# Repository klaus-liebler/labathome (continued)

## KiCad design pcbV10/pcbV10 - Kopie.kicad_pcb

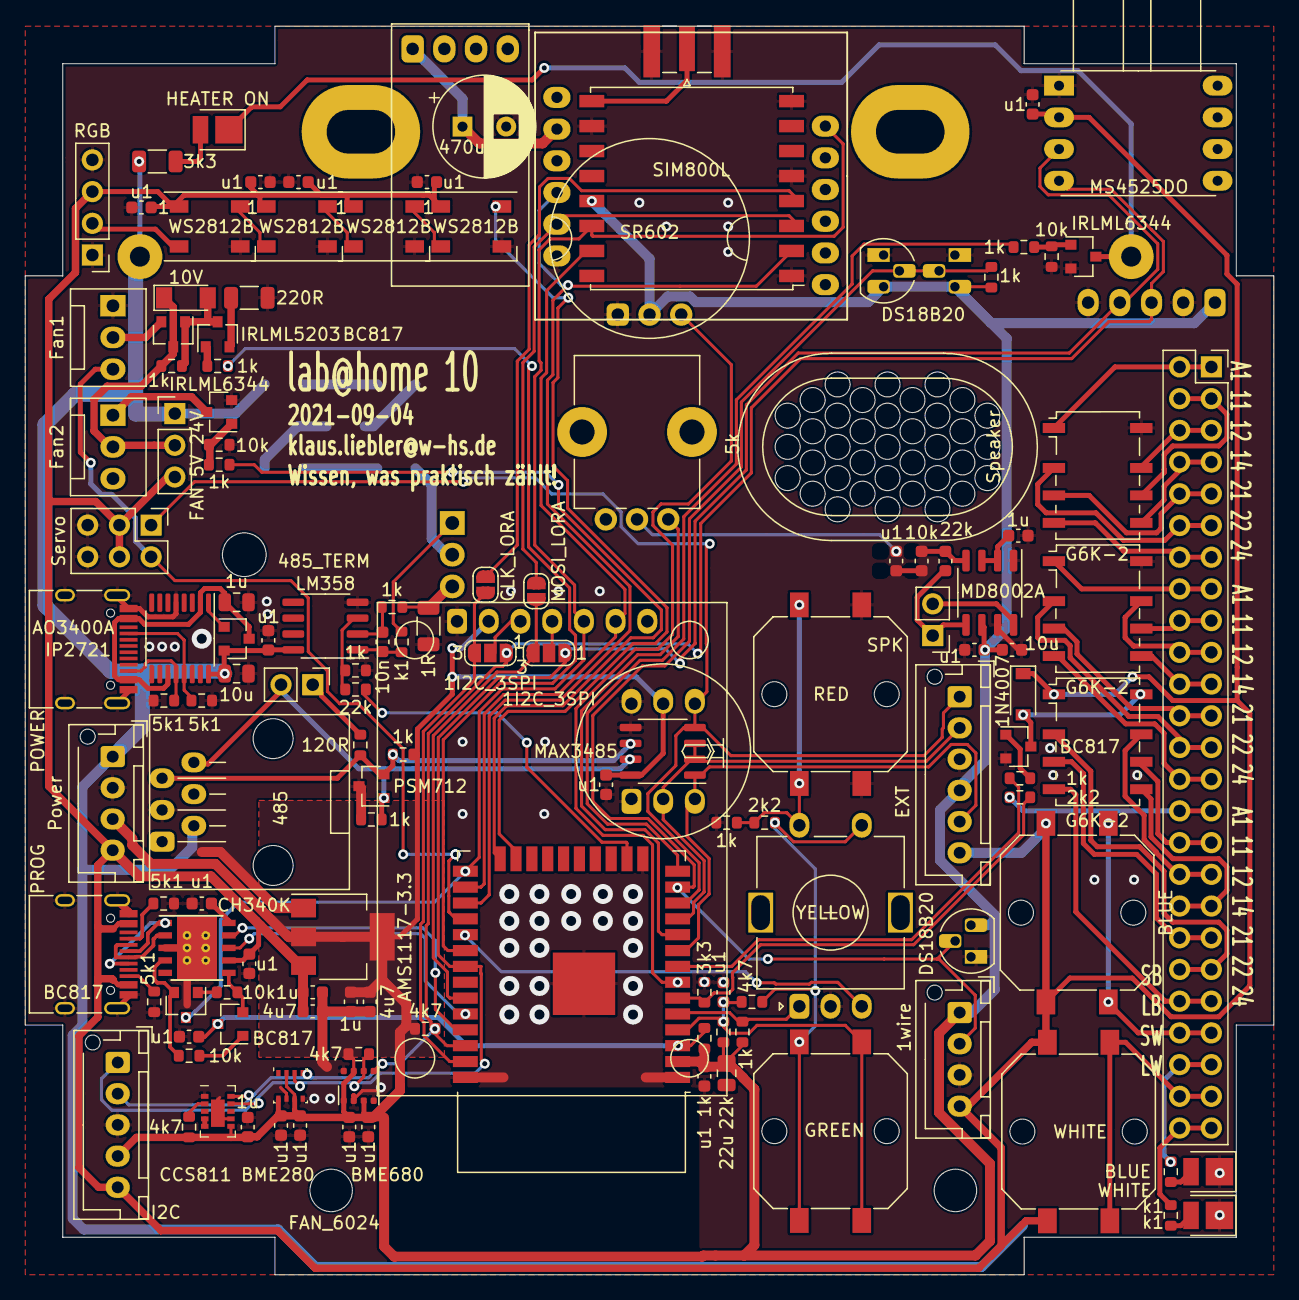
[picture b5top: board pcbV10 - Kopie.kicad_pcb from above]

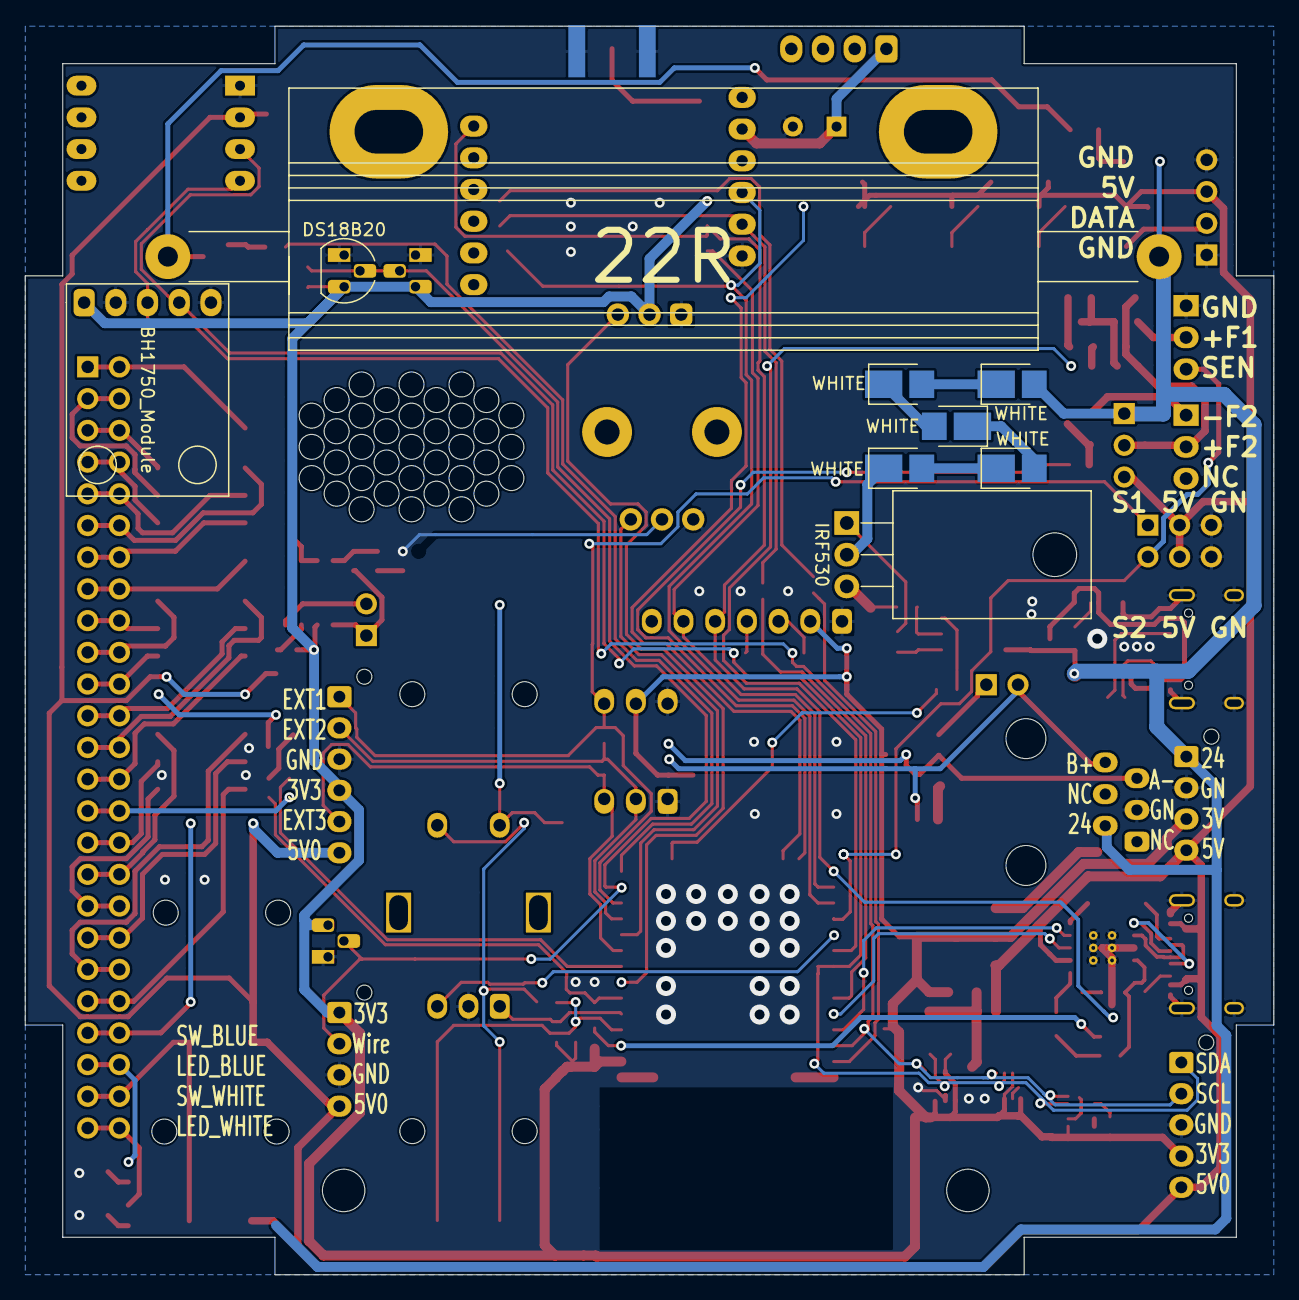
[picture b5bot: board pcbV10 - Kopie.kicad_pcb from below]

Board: 2 copper layers, 100.0 x 100.0 mm, 146 parts (9 on the bottom side), 116 nets.

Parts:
C1, C8: 4u7; C_0603_1608Metric
C2: 22u; C_0805_2012Metric
C3, C9, C23, C30: 1u; C_0603_1608Metric
C4, C5, C6, C7, C10, C11, C12, C13, C14, C15, C16, C18, C20, C21, C24, C25, C28, C29: u1; C_0603_1608Metric
C17: 1u; C_0805_2012Metric
C19: 10u; C_0805_2012Metric
C22: 10n; C_0603_1608Metric
C26: 10u; C_0603_1608Metric
C27: 470u; CP_Radial_D8.0mm_P3.50mm
D1, D2, D3, D15: WS2812B; LED_WS2812B_PLCC4_5.0x5.0mm_P3.2mm
D4: PSM712; SOT-23
D5: 1N4007; D_SOD-123
D6: HEATER ON; LED_PLCC_2835
D7: WHITE; LED_PLCC_2835
D8: BLUE; LED_PLCC_2835
D9: 10V; D_MiniMELF
D10, D11, D12, D13, D14: WHITE; LED_PLCC_2835_Handsoldering
GSM_Module1: SIM800L
J1: PROG; USB_C_Receptacle_HRO_TYPE-C-31-M-12
J2: Servo; PinHeader_2x03_P2.54mm_Vertical
J3: I2C; JST_XH_B5B-XH-AM_1x05_P2.50mm_Vertical
J4: 1wire; JST_XH_B4B-XH-AM_1x04_P2.50mm_Vertical
J5: EXT; JST_XH_B6B-XH-AM_1x06_P2.50mm_Vertical
J6: Power; JST_XH_B4B-XH-AM_1x04_P2.50mm_Vertical
J7: 485; WR_MJ_Modular_Jack_Vertical_Plastic_6P6C
J8: POWER; USB_C_Receptacle_HRO_TYPE-C-31-M-12
J9: RGB; PinHeader_1x04_P2.54mm_Vertical
J10: Fan1; FanPinHeader_1x03_P2.54mm_Vertical
J11: Fan2; FanPinHeader_1x03_P2.54mm_Vertical
J12: VPS; PinSocket_2x25_P2.54mm_Vertical
J13: SPK; PinHeader_1x02_P2.54mm_Vertical
J14: LoRa; SMA_Samtec_SMA-J-P-X-ST-EM1_EdgeMount
JP1: 485_TERM; PinHeader_1x02_P2.54mm_Vertical
JP2: FAN 5V 24V; PinHeader_1x03_P2.54mm_Vertical
JP3, JP4: 1I2C_3SPI; SolderJumper-3_P1.3mm_Open_RoundedPad1.0x1.5mm_NumberLabels
JP6: MOSI_LORA; SolderJumper-2_P1.3mm_Open_RoundedPad1.0x1.5mm
JP7: CLK_LORA; SolderJumper-2_P1.3mm_Open_RoundedPad1.0x1.5mm
K1, K2, K3: G6K-2; Relay_DPDT_Omron_G6K-2F-Y
Q1, Q2, Q4, Q6: BC817; SOT-23
Q3: AO3400A; SOT-23
Q5, Q9: IRLML6344; SOT-23
Q7: IRLML5203; SOT-23
Q8: IRF530; TO-220-3_Horizontal_TabDown
R1, R4, R11, R12, R14, R15, R17, R23, R27, R28, R29, R32, R34: 1k; R_0603_1608Metric
R2, R3, R9, R10: 5k1; R_0603_1608Metric
R5, R8, R21, R40: 4k7; R_0603_1608Metric
R6, R7, R16, R35: 10k; R_0603_1608Metric
R13: 120R; R_0603_1608Metric
R18: 22R; Resistor_100W
R19: 3k3; R_1206_3216Metric
R20, R26: 22k; R_0603_1608Metric
R22, R37: 2k2; R_0603_1608Metric
R24, R25, R31: k1; R_0603_1608Metric
R30: 220R; R_1206_3216Metric
R33: 1R; R_1206_3216Metric
R36: 3k3; R_0603_1608Metric
R38: 10k; C_0603_1608Metric
R39: 22k; C_0603_1608Metric
RV1: 5k; Potentiometer_Alps_RK09K_Single_Vertical
SP1: Speaker; SPEAKER_2415
SW1: BLUE; SW_Push_1P1T_NO_CK_PTS125Sx43PSMTR
SW2: YELLOW; RotaryEncoder_Alps_EC11E-Switch_Vertical_H20mm
SW3: GREEN; SW_Push_1P1T_NO_CK_PTS125Sx43PSMTR
SW4: RED; SW_Push_1P1T_NO_CK_PTS125Sx43PSMTR
SW5: WHITE; SW_Push_1P1T_NO_CK_PTS125Sx43PSMTR
U1: AMS1117-3.3; SOT-223-3_TabPin2
U2: ESP32-WROOM-32
U3: CH340K; SSOP-10_3.9x4.9mm_P1.00mm_EP
U4: MS4525DO
U5: INMP441_Module
U6: MAX3485; SO-8_3.9x4.9mm_P1.27mm
U7: BME680; Bosch_LGA-8_3x3mm_P0.8mm_ClockwisePinNumbering
U8: IP2721; TSSOP-16_4.4x5mm_P0.65mm
U9: BH1750_Module; GY-302
U10: SR602; PIR_Sensor_SR602
U11: LM358; SO-8_3.9x4.9mm_P1.27mm
U12, U13, U15: DS18B20; TO-92_HandSolder
U14: IPS_240_240; IPS_240_240_1.3
U16: MODULE_STEPDOWN
U17: RFM95W-868S2; HOPERF_RFM9XW_SMD
U18: MD8002A; SO-8_3.9x4.9mm_P1.27mm
U19: BME280; Bosch_LGA-8_2.5x2.5mm_P0.65mm_ClockwisePinNumbering
U20: CCS811; AMS_LGA-10-1EP_2.7x4mm_P0.6mm
X1: FAN_6024

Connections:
1wire: J4.2, R4.1, U2.13, U12.2, U13.2, U15.2
485_DE: J5.2, U2.11, U5.2, U6.2, U6.3
485_DI: J2.1, J5.1, U2.12, U5.4, U6.4
485_RO: J5.5, U2.9, U5.3, U6.1
+3V3: C2.1, C4.2, C8.2, C9.1, C11.2, C12.2, C13.2, C25.1, C26.1, C28.2, C29.2, C30.1, J3.4, J4.1, J5.4, J6.3, R1.2, R4.2, R5.2, R8.2, R12.1, R17.2, R20.1, R40.2, U1.2, U2.2, U5.5, U6.8, U7.2, U7.6, U7.8, U9.1, U10.2, U12.3, U13.3, U14.2, U15.3, U17.13, U18.6, U19.2, U19.6, U19.8, U20.6
+4V: C27.1, GSM_Module1.2, U16.1
+5V: C1.2, C3.1, C6.2, C7.2, C14.2, C15.2, C16.2, C18.2, D1.1, D2.1, D3.1, D5.1, D15.1, J1.A4, J1.A9, J1.B4, J1.B9, J2.3, J2.4, J3.5, J4.4, J5.6, J6.4, J9.3, JP2.3, K3.1, SW1.1, SW5.1, U1.3, U3.7, U4.2
+24V: C19.1, C21.1, D14.2, J6.1, J7.2, JP2.1, Q3.2, R18.1, R19.1, U8.16, U11.8
/C: JP3.2, U14.3
/D: JP4.2, U14.4
/DTR: Q2.2, R6.2, U3.4
/RTS: Q1.2, R7.2, U3.6
/VBUS: C17.2, J8.A4, J8.A9, J8.B4, J8.B9, Q3.3, U8.2, U8.11
/wireless/SPI_CLKx: JP7.2, U17.4
AUDIO: RV1.1, U2.10
FAN1_DRIVE: R28.2, U2.30
FAN1_SENSE: J2.2, J10.3, U2.28
FAN2_DRIVE: R34.2, U2.24
GND: C1.1, C2.2, C3.2, C4.1, C5.1, C6.1, C7.1, C8.1, C9.2, C10.2, C11.1, C12.1, C13.1, C14.1, C15.1, C16.1, C17.1, C18.1, C19.2, C20.1, C21.2, C23.2, C25.2, C26.2, C27.2, C28.1, C29.1, C30.2, D1.3, D2.3, D3.3, D4.3, D7.1, D8.1, D15.3, GSM_Module1.6, J1.A1, J1.A12, J1.B1, J1.B12, J1.S1, J2.5, J2.6, J3.3, J4.3, J5.3, J6.2, J7.3, J8.A1, J8.A12, J8.B1, J8.B12, J8.S1, J9.1, J9.4, J10.1, J14.2, K1.8, K2.8, Q4.2, Q5.2, Q9.2, R2.1, R3.1, R9.1, R10.1, R11.2, R16.1, R23.1, R27.1, R30.1, R33.2, R35.1, R36.1, RV1.3, SW2.C, SW4.1, U1.1, U2.1, U2.15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
HEATER: R15.2, U2.14
K1_11: J12.3, J12.4, K1.6
K1_12: J12.5, J12.6, K1.7
K1_14: J12.7, J12.8, K1.5
K1_21: J12.9, J12.10, K1.3
K1_22: J12.11, J12.12, K1.2
K1_24: J12.13, J12.14, K1.4
K1_A1: J12.1, J12.2, K1.1
K2_11: J12.17, J12.18, K2.6
K2_12: J12.19, J12.20, K2.7
K2_14: J12.21, J12.22, K2.5
K2_21: J12.23, J12.24, K2.3
K2_22: J12.25, J12.26, K2.2
K2_24: J12.27, J12.28, K2.4
K2_A1: J12.15, J12.16, K2.1
K3_11: J12.31, J12.32, K3.6
K3_12: J12.33, J12.34, K3.7
K3_14: J12.35, J12.36, K3.5
K3_21: J12.37, J12.38, K3.3
K3_22: J12.39, J12.40, K3.2
K3_24: J12.41, J12.42, K3.4
K3_A1: R36.2, R37.1, U2.6
K3_ON: R14.2, U2.8
LED_BLUE: J12.45, J12.46, R25.2
LED_RGB: D1.4, U2.23
LED_WHITE: J12.49, J12.50, R24.2
LED_WHITE_P: R26.2, U2.16
MOVE: U2.7, U10.3
unnamed: C10.1, U3.10
unnamed: C22.1, R32.1, U11.2
unnamed: C22.2, R31.1, U11.1
unnamed: C23.1, U18.2, U18.3
unnamed: C24.1, R38.2
unnamed: C24.2, RV1.2
unnamed: D1.2, D2.4
unnamed: D2.2, D3.4
unnamed: D5.2, K3.8, Q4.3
unnamed: D6.1, Q5.3, R18.2
unnamed: D6.2, R19.2
unnamed: D7.2, R24.1
unnamed: D8.2, R25.1
unnamed: D9.1, J11.2, JP2.2, Q7.3, R29.2
unnamed: D9.2, Q6.3, Q7.1, R29.1
unnamed: D10.1, D11.2
unnamed: D10.2, D12.1
unnamed: D11.1, D13.2
unnamed: D12.2, D14.1
unnamed: D13.1, Q8.2
unnamed: D15.2, J9.2
unnamed: D3.2, D15.4
unnamed: J1.A5, R2.2
unnamed: J1.A6, J1.B6, U3.1
unnamed: J1.A7, J1.B7, U3.2
unnamed: J1.B5, R3.2
unnamed: J8.A5, R9.2, U8.13
unnamed: J8.B5, R10.2, U8.12
unnamed: J10.2, Q7.2
unnamed: J11.1, Q9.3
unnamed: J12.29, J12.30, R37.2
unnamed: J13.1, R39.1, U18.5
unnamed: J13.2, U18.8
unnamed: J14.1, U17.9
unnamed: JP1.1, R13.2
unnamed: Q1.1, R6.1
unnamed: Q2.1, R7.1
unnamed: Q3.1, U8.1
unnamed: Q4.1, R14.1
unnamed: Q5.1, R15.1, R16.2
unnamed: Q6.1, R28.1
unnamed: Q6.2, R30.2
unnamed: Q8.1, R31.2
unnamed: Q8.3, R32.2, R33.1
unnamed: Q9.1, R34.1, R35.2
unnamed: R21.1, R22.2, SW2.S1, SW3.1
unnamed: R22.1, R23.2, SW2.S2, SW4.2
unnamed: R26.1, R27.2, U11.3
unnamed: R38.1, R39.2, U18.4
unnamed: R40.1, U20.2
unnamed: U20.4, U20.5
PROG_EN: C5.2, Q1.3, R1.1, U2.3
PROG_IO0: GSM_Module1.7, Q2.3, U2.25, U14.5, U17.14
PROG_RX: U2.35, U3.9
PROG_TX: U2.34, U3.8
ROT_A: R17.1, SW2.A, U2.5
ROT_B: SW2.B, U2.29
RS485A: D4.2, J7.5, R12.2, R13.1, U6.6
RS485B: D4.1, J7.6, JP1.2, R11.1, U6.7
SCL: J3.2, JP3.1, R8.1, U2.36, U4.4, U7.4, U9.3, U19.4, U20.10
SDA: J3.1, JP4.1, R5.1, U2.31, U4.3, U7.3, U9.4, U19.3, U20.9
SPI_CLK: JP3.3, JP7.1, U2.37
SPI_IO1: U2.26, U14.6, U17.15
SPI_MISO: GSM_Module1.4, U2.27, U17.2
SPI_MOSI: JP4.3, JP6.1, U2.33
SPI_MOSIx: GSM_Module1.5, JP6.2, U17.3
SW: C20.2, R20.2, R21.2, SW3.2, U2.4
SW_BLUE: J12.43, J12.44, SW1.2
SW_WHITE: J12.47, J12.48, SW5.2

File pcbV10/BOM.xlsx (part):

Reference | Quantity | Value | Footprint | Datasheet | AVAILABILITY | DESCRIPTION | MF | MP | PACKAGE | PRICE | Option | Description.1 | Height | Manufacturer_Name | Manufacturer_Part_Number
C1 C8 | 2 | 4u7 | Capacitor_SMD:C_0603_1608Metric | ~
C4 C5 C6 C7 C10 C11 C12 C13 C14 C15 C16 C18 C20 C24 C25 C28 C29 C31 C34 C35 | 20 | u1 | Capacitor_SMD:C_0603_1608Metric | ~
C17 C21 | 2 | 1u | Capacitor_SMD:C_1206_3216Metric | ~
C19 C22 C32 | 3 | 10u | Capacitor_SMD:C_1206_3216Metric | ~
C2 | 1 | 22u | Capacitor_SMD:C_0603_1608Metric | ~
C26 | 1 | 10u | Capacitor_SMD:C_0603_1608Metric | ~ |  |  |  |  |  |  | Sound only
C27 | 1 | 470u | Capacitor_THT:CP_Radial_D8.0mm_P3.50mm | ~
C3 C9 C23 C30 | 4 | 1u | Capacitor_SMD:C_0603_1608Metric | ~
C33 | 1 | u1 | Capacitor_SMD:C_0805_2012Metric | ~
C36 C37 | 2 | 22u | Capacitor_SMD:C_0805_2012Metric | ~
D1 D2 D3 D15 | 4 | WS2812B | LED_SMD:LED_WS2812B_PLCC4_5.0x5.0mm_P3.2mm | https://cdn-shop.adafruit.com/datasheets/WS2812B.pdf
D16 | 1 | Schttky | Diode_SMD:D_SOD-123 | ~
D4 | 1 | PSM712 | Package_TO_SOT_SMD:SOT-23 | http://www.onsemi.com/pub_link/Collateral/NUP2105L-D.PDF
D5 | 1 | 1N4007 | Diode_SMD:D_SOD-123 | ~
D6 | 1 | HEATER ON | liebler_OPTO:LED_PLCC_2835 | ~
D7 D10 D11 D12 D13 D14 | 6 | WHITE | liebler_OPTO:LED_PLCC_2835 | ~
D8 | 1 | BLUE | liebler_OPTO:LED_PLCC_2835 | ~
D9 | 1 | 10V | Diode_SMD:D_MiniMELF | ~
FID1 FID2 | 2 | Fiducial | Fiducial:Fiducial_1mm_Mask2mm | ~
GSM_Module1 | 1 | SIM800L | liebler_MODULES:SIM800L
IMG1 | 1 | Speaker | liebler_DRAWINGS:speaker | ~
IMG2 | 1 | Augenschutz | liebler_DRAWINGS:augenschutz | ~
IMG3 | 1 | HOT | liebler_DRAWINGS:hot | ~
IMG4 | 1 | WHS | liebler_DRAWINGS:LOGO_WHS | ~
J1 | 1 | PROG | liebler_CONN:USB_C_Receptacle_HRO_TYPE-C-31-M-12_IMPROVED | https://www.usb.org/sites/default/files/documents/usb_type-c.zip
J10 | 1 | Fan1 | Connector:FanPinHeader_1x03_P2.54mm_Vertical | ~
J11 | 1 | Fan2 | Connector:FanPinHeader_1x03_P2.54mm_Vertical | ~
J12 | 1 | VPS | Connector_PinSocket_2.54mm:PinSocket_2x25_P2.54mm_Vertical | ~
J13 | 1 | SPK | Connector_PinHeader_2.54mm:PinHeader_1x02_P2.54mm_Vertical | ~
J14 | 1 | LoRa | Connector_Coaxial:SMA_Samtec_SMA-J-P-X-ST-EM1_EdgeMount | ~
J15 | 1 | 1B 2A | Connector_Phoenix_MC:PhoenixContact_MCV_1,5_2-G-3.81_1x02_P3.81mm_Vertical | ~
J16 | 1 | BME280 | Connector_PinSocket_2.54mm:PinSocket_1x06_P2.54mm_Vertical | ~
J17 | 1 | CCS811 | Connector_PinSocket_2.54mm:PinSocket_1x08_P2.54mm_Vertical | ~
J2 | 1 | Servo | Connector_PinHeader_2.54mm:PinHeader_2x03_P2.54mm_Vertical | ~
J3 | 1 | I2C | Connector_JST:JST_XH_B5B-XH-AM_1x05_P2.50mm_Vertical | ~
J4 | 1 | 1wire | Connector_JST:JST_XH_B4B-XH-AM_1x04_P2.50mm_Vertical | ~
J5 | 1 | EXT | Connector_JST:JST_XH_B6B-XH-AM_1x06_P2.50mm_Vertical | ~
J6 | 1 | 5V 3V GN 24 | Connector_JST:JST_XH_B4B-XH-AM_1x04_P2.50mm_Vertical | ~
J7 | 1 | 485 | liebler_CONN:WR_MJ_Modular_Jack_Vertical_Plastic_6P6C | ~
J8 | 1 | POWER | liebler_CONN:USB_C_Receptacle_HRO_TYPE-C-31-M-12_IMPROVED | https://www.usb.org/sites/default/files/documents/usb_type-c.zip
J9 | 1 | RGB | Connector_PinHeader_2.54mm:PinHeader_1x04_P2.54mm_Vertical | ~
JP3 JP4 | 2 | 1I2C_3SPI | Jumper:SolderJumper-3_P1.3mm_Open_RoundedPad1.0x1.5mm_NumberLabels | ~
JP6 | 1 | MOSI_LORA | Jumper:SolderJumper-2_P1.3mm_Open_RoundedPad1.0x1.5mm | ~
JP7 | 1 | CLK_LORA | Jumper:SolderJumper-2_P1.3mm_Open_RoundedPad1.0x1.5mm | ~
K1 K2 K3 | 3 | G6K-2 | Relay_SMD:Relay_DPDT_Omron_G6K-2F-Y | http://omronfs.omron.com/en_US/ecb/products/pdf/en-g6k.pdf
L1 | 1 | 47u | Inductor_SMD:L_Wuerth_HCI-7030 | ~
L2 | 1 | 10uH | liebler_PASSIVES:ASPIAIG-Q8080 | ~
MK1 | 1 | ICS-43434 | liebler_SEMICONDUCTORS:MIC_ICS-43434 |  | Bad | Multi-Mode Microphone with I2S Digital Output | TDK-InvenSense | ICS-43434 | LGA-6 TDK-InvenSense | 2.43 USD
Q1 Q2 Q4 Q6 | 4 | BC817 | Package_TO_SOT_SMD:SOT-23 | https://www.onsemi.com/pub/Collateral/BC818-D.pdf
Q3 | 1 | AO3400A | Package_TO_SOT_SMD:SOT-23 | http://www.aosmd.com/pdfs/datasheet/AO3400A.pdf
Q5 Q9 | 2 | IRLML6344 | Package_TO_SOT_SMD:SOT-23 | https://www.infineon.com/dgdl/irlml0030pbf.pdf?fileId=5546d4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
Q7 | 1 | IRLML5203 | Package_TO_SOT_SMD:SOT-23 | https://www.infineon.com/dgdl/irlml5203pbf.pdf?fileId=5546d4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
R13 | 1 | 120R | Resistor_SMD:R_0603_1608Metric | ~
R1 R4 R11 R12 R14 R15 R17 R23 R28 R29 R34 R44 | 12 | 1k | Resistor_SMD:R_0603_1608Metric | ~
R18 | 1 | 22R | liebler_PASSIVES:Resistor_100W | ~
R19 | 1 | 3k3 | Resistor_SMD:R_1206_3216Metric | ~
R20 | 1 | 22k | Resistor_SMD:R_0603_1608Metric | ~
R5 R8 R21 R40 | 4 | 4k7 | Resistor_SMD:R_0603_1608Metric | ~
R22 R37 | 2 | 2k2 | Resistor_SMD:R_0603_1608Metric | ~
R24 R25 | 2 | k1 | Resistor_SMD:R_0603_1608Metric | ~
R27 | 1 | 1M | Resistor_SMD:R_0603_1608Metric | ~
R30 | 1 | 220R | Resistor_SMD:R_1206_3216Metric | ~
R31 | 1 | 51k | Resistor_SMD:R_0603_1608Metric | ~
R32 | 1 | 22R | Resistor_SMD:R_0603_1608Metric | ~
R33 | 1 | R68 | Resistor_SMD:R_1206_3216Metric | ~
R36 | 1 | 3k3 | Resistor_SMD:R_0603_1608Metric | ~
R38 | 1 | 10k | Capacitor_SMD:C_0603_1608Metric | ~ |  |  |  |  |  |  | Sound only
R39 | 1 | 22k | Capacitor_SMD:C_0603_1608Metric | ~ |  |  |  |  |  |  | Sound only
R41 R43 | 2 | M1 | Resistor_SMD:R_0603_1608Metric | ~
R42 | 1 | 2k2 | Capacitor_SMD:C_0603_1608Metric | ~ |  |  |  |  |  |  | Sound only
R45 | 1 | 6k8 | Resistor_SMD:R_0603_1608Metric | ~
R46 | 1 | 39k | Resistor_SMD:R_0603_1608Metric | ~
R47 | 1 | k47 | Resistor_SMD:R_0603_1608Metric | ~
R6 R7 R16 R26 R35 | 5 | 10k | Resistor_SMD:R_0603_1608Metric | ~
R2 R3 R9 R10 | 4 | 5k1 | Resistor_SMD:R_0603_1608Metric | ~
RV1 | 1 | 1k | Potentiometer_THT:Potentiometer_Alps_RK09K_Single_Vertical | ~ |  |  |  |  |  |  | Sound only
SP1 | 1 | Speaker | liebler_MECH:SPEAKER_2415 | ~
SW1 | 1 | BTN BLUE | liebler_MECH:SW_Push_1P1T_NO_CK_PTS125Sx43PSMTR | ~
SW10 | 1 | 5V FAN 24V | liebler_MECH:Switch_SS12D00 | ~
SW11 | 1 | 24V->5V | liebler_MECH:Switch_SS12D00 | ~
SW2 | 1 | YELLOW | liebler_MECH:RotaryEncoder_Alps_EC11E-Switch_Vertical_H20mm | ~
SW3 | 1 | GREEN | liebler_MECH:SW_Push_1P1T_NO_CK_PTS125Sx43PSMTR | ~
SW4 | 1 | RED | liebler_MECH:SW_Push_1P1T_NO_CK_PTS125Sx43PSMTR | ~
SW5 | 1 | BTN WHITE | liebler_MECH:SW_Push_1P1T_NO_CK_PTS125Sx43PSMTR | ~
SW6 | 1 | TERM ON | liebler_MECH:Switch_SS12D00 | ~
SW7 | 1 | LED HEATER | liebler_MECH:Switch_SS12D00 | ~
SW8 | 1 | REL_ROT | liebler_MECH:Switch_SS12D00 | ~
SW9 | 1 | SNS MOV | liebler_MECH:Switch_SS12D00 | ~
U1 | 1 | AMS1117-3.3 | Package_TO_SOT_SMD:SOT-223-3_TabPin2 | http://www.advanced-monolithic.com/pdf/ds1117.pdf
U10 | 1 | SR602 | liebler_MODULES:PIR_Sensor_SR602
U11 | 1 | MP4420 | Package_TO_SOT_SMD:TSOT-23-8
U12 U13 U15 | 3 | DS18B20 | Package_TO_SOT_THT:TO-92_HandSolder | http://datasheets.maximintegrated.com/en/ds/DS18B20.pdf
U14 | 1 | IPS_240_240 | liebler_OPTO:IPS_240_240_1.3
U16 | 1 | MODULE_STEPDOWN | liebler_MODULES:MODULE_STEPDOWN
U17 | 1 | RFM95W-868S2 | RF_Module:HOPERF_RFM9XW_SMD | https://www.hoperf.com/data/upload/portal/20181127/5bfcbea20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
U18 | 1 | MD8002A | Package_SO:SOIC-8_3.9x4.9mm_P1.27mm | https://www.sunrom.com/get/408862 |  |  |  |  |  |  |  | Audio Amplifier, SOP8 | 175 | Sunrom | MD8002A
U19 | 1 | BME280 | Package_LGA:Bosch_LGA-8_2.5x2.5mm_P0.65mm_ClockwisePinNumbering | https://ae-bst.resource.bosch.com/media/_tech/media/datashee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
U2 | 1 | ESP32-WROOM-32 | RF_Module:ESP32-WROOM-32 | https://www.espressif.com/sites/default/files/documentation/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
U20 | 1 | CCS811 | liebler_SEMICONDUCTORS:AMS_LGA-10-1EP_2.7x4mm_P0.6mm | http://ams.com/eng/Products/Environmental-Sensors/Air-Qualit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
U3 | 1 | CH340K | liebler_SEMICONDUCTORS:SSOP-10_3.9x4.9mm_P1.00mm_EP
U4 | 1 | MS4525DO | liebler_MODULES:MS4525DO
U5 | 1 | ZXLD1350 | Package_TO_SOT_SMD:SOT-23-5
U6 | 1 | MAX3485 | Package_SO:SOIC-8_3.9x4.9mm_P1.27mm | https://datasheets.maximintegrated.com/en/ds/MAX3483-MAX3491.pdf
U7 | 1 | BME680 | Package_LGA:Bosch_LGA-8_3x3mm_P0.8mm_ClockwisePinNumbering | https://ae-bst.resource.bosch.com/media/_tech/media/datashee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

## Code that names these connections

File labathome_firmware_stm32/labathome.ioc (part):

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Mcu.Name=STM32G431C(6-8-B)Ux
Mcu.Package=UFQFPN48
Mcu.UserName=STM32G431CBUx
PA0.GPIOParameters=GPIO_Label
PA0.GPIO_Label=ENC_A
PA0.Signal=S_TIM2_CH1
PA1.GPIOParameters=GPIO_Label
PA1.GPIO_Label=ENC_B
PA1.Signal=S_TIM2_CH2
PA10.GPIOParameters=GPIO_Label
PA10.GPIO_Label=BL_DRV3
PA10.Signal=S_TIM1_CH3
PA11.Mode=Device
PA11.Signal=USB_DM
PA12.Mode=Device
PA12.Signal=USB_DP
PA13.Signal=SYS_JTMS-SWDIO
PA14.Signal=SYS_JTCK-SWCLK
PA15.Mode=I2C
PA15.Signal=I2C1_SCL
PA2.GPIOParameters=GPIO_Label
PA2.GPIO_Label=Servo1
PA2.Signal=S_TIM15_CH1
PA3.GPIOParameters=GPIO_Label
PA3.GPIO_Label=Servo2
PA3.Signal=S_TIM15_CH2
PA4.Signal=COMP_DAC11_group
PA5.Signal=COMP_DAC12_group
PA6.GPIOParameters=GPIO_Label
PA6.GPIO_Label=Servo3
PA6.Signal=S_TIM16_CH1
PA7.GPIOParameters=GPIO_Label
PA7.GPIO_Label=Fan
PA7.Signal=S_TIM17_CH1
PA8.GPIOParameters=GPIO_Label
PA8.GPIO_Label=BL_DRV1
PA8.Signal=S_TIM1_CH1
PA9.GPIOParameters=GPIO_Label
PA9.GPIO_Label=BL_DRV2
PA9.Signal=S_TIM1_CH2
PB0.GPIOParameters=GPIO_Label
PB0.GPIO_Label=Hall2
PB0.Signal=S_TIM3_CH3
PB1.GPIOParameters=GPIO_Label
PB1.GPIO_Label=Hall3
PB1.Signal=S_TIM3_CH4
PB11.GPIOParameters=GPIO_Label
PB11.GPIO_Label=RELAY
PB11.Signal=GPIO_Output
PB12.GPIOParameters=GPIO_Label
PB12.GPIO_Label=BL_RESET
PB12.Signal=GPIO_Input
PB13.GPIOParameters=GPIO_Label
PB13.GPIO_Label=BL_FAULT
PB13.Signal=GPIO_Input
PB14.GPIOParameters=GPIO_Label
PB14.GPIO_Label=ADC1
PB14.Mode=IN5-Single-Ended
PB14.Signal=ADC1_IN5
PB15.GPIOParameters=GPIO_Label
PB15.GPIO_Label=ADC2
PB15.Signal=SharedAnalog_PB15
PB2.GPIOParameters=GPIO_Label
PB2.GPIO_Label=BRIGHTNESS
PB2.Mode=IN12-Single-Ended
PB2.Signal=ADC2_IN12
PB3.GPIOParameters=GPIO_Label
PB3.GPIO_Label=LED_INFO
PB3.Signal=GPIO_Output
PB4.Mode=Sink_AllSignals
PB4.Signal=UCPD1_CC2
PB5.GPIOParameters=GPIO_Label
PB5.GPIO_Label=BL_HALL3
PB5.Signal=S_TIM3_CH2
PB6.Mode=Sink_AllSignals
PB6.Signal=UCPD1_CC1
PB7.Mode=I2C
PB7.Signal=I2C1_SDA
PB8-BOOT0.GPIOParameters=GPIO_Label
PB8-BOOT0.GPIO_Label=BTN_RED
PB8-BOOT0.Signal=GPIO_Input
PB9.GPIOParameters=GPIO_Label
PB9.GPIO_Label=LED_POWER
PB9.Signal=S_TIM4_CH4
PC10.Mode=Asynchronous
PC10.Signal=UART4_TX
PC11.Mode=Asynchronous
PC11.Signal=UART4_RX
PC13.GPIOParameters=GPIO_Label
PC13.GPIO_Label=BTN_YEL
PC13.Signal=GPIO_Input
PC14-OSC32_IN.GPIOParameters=GPIO_Label
PC14-OSC32_IN.GPIO_Label=MOVEMENT_SENSOR
PC14-OSC32_IN.Signal=GPIO_Input
PC4.GPIOParameters=GPIO_Label
PC4.GPIO_Label=Heater
PC4.Signal=GPIO_Output
PC6.GPIOParameters=GPIO_Label
PC6.GPIO_Label=BL_ENABLE_OR_LED
PC6.Signal=GPIO_Output
PF0-OSC_IN.Mode=HSE-External-Oscillator
PF0-OSC_IN.Signal=RCC_OSC_IN
PF1-OSC_OUT.Mode=HSE-External-Oscillator
PF1-OSC_OUT.Signal=RCC_OSC_OUT
RCC.HSE_VALUE=8000000
RCC.SYSCLKFreq_VALUE=170000000
RCC.SYSCLKSource=RCC_SYSCLKSOURCE_PLLCLK
board=custom

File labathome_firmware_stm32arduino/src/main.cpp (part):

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float brushless_motor_velocity{0.0};
constexpr int POLE_PAIRS{7};
BLDCMotor bldcmotor = BLDCMotor(POLE_PAIRS);
BLDCDriver3PWM bldcdriver = BLDCDriver3PWM(PIN::BL_DRV1, PIN::BL_DRV2, PIN::BL_DRV3, PIN::BL_ENABLE);

constexpr time_t TIMEOUT_FOR_FAILSAFE{3000};
bool alreadySetToFailsafe{false};
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OPAMP_HandleTypeDef hopamp3;
HardwareSerial StepperSerial(PIN::UART3_RX, PIN::UART3_TX);
//Important: Define TX-Pin in the "const PinMap PinMap_UART_TX[]"-structure as OpenDrain
HardwareSerial ServoBusSerial(PIN::ADC1_U1R, PIN::ADC0_U1T);
// TMC2209Stepper stepperdriver(PIN::UART3_RX, PIN::UART3_TX, R_SENSE, DRIVER_ADDRESS);
HardwareSerial & stepper_serial_stream = StepperSerial;
TMC2209 stepperdriver;
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#if defined(ARDUINO_LABATHOME_15_0) || defined(ARDUINO_LABATHOME_15_1) || defined(ARDUINO_LABATHOME_15_2)
  digitalWrite(PIN::RELAY, e2s_buffer.Relay);
#endif
  digitalWrite(PIN::BL_RESET, e2s_buffer.Blreset);
#if defined(ARDUINO_LABATHOME_15_1) || defined(ARDUINO_LABATHOME_15_2) || defined(ARDUINO_LABATHOME_15_3)
  digitalWrite(PIN::BL_SLEEP, e2s_buffer.Blsleep);
  // digitalWrite(PIN::LCD_RESET, e2s_buffer.LcdReset);
#endif
  // TODO USBC
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  led->Loop(now);

  // I2C_SLAVE::e2s_buffer[E2S::HEATER_POS] = encoder.GetTicks(); // COMMENT OUT FOR TESTING ONLY
  s2e_buffer.ButtonRed = digitalRead(PIN::BTN_RED);
  s2e_buffer.ButtonYellow = (!digitalRead(PIN::BTN_YELLOW));
  s2e_buffer.Movement = digitalRead(PIN::MOVEMENT);
  s2e_buffer.Blfault = (!digitalRead(PIN::BL_FAULT));
  s2e_buffer.Rotenc = encoder.GetTicks();
  s2e_buffer.Brightness = analogRead(PIN::BRIGHTNESS);
  s2e_buffer.UsbpdVoltage_mv = PowerSink.activeVoltage;
  //s2e_buffer.Adc0 = analogRead(PIN::ADC_0_U1T);
  //s2e_buffer.Adc1 = analogRead(PIN::ADC_1_U1R);
#if defined(ARDUINO_LABATHOME_15_2) || defined(ARDUINO_LABATHOME_15_3)
  s2e_buffer.PIN_PB12 = digitalRead(PIN::PIN_PB12);
  s2e_buffer.Adc2_24V = analogRead(PIN::ADC_2_24V);
// s2e_buffer.Adc3_Bl_i_sense=analogRead(PIN::BL_ISENSE); wrong, we do not read the input directly, but the OPAMPs output
#endif

  if (now >= timeToPutActorsInFailsafe)
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    if (e2s_buffer.Heater > 0)
    {
      if(!heaterBefore){
        digitalWrite(PIN::HEATER, HIGH);
        log_info("Heater ON");
      }
      heaterBefore=true;
    }
    else
    {
      digitalWrite(PIN::HEATER, LOW);
      heaterBefore=false;
    }
  }
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    if(heaterBefore){
      log_info("Heater OFF");
    }
    digitalWrite(PIN::HEATER, LOW);
    heaterBefore=false;
  }
}
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void setup()
{

  led = new SINGLE_LED::M(PIN::LED_INFO, true, &WAITING_FOR_CONNECTION);
  led->Begin(millis(), &WAITING_FOR_CONNECTION, 10000);  
  Serial.begin(115200);
  
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  Serial4.printf("Application started Serial4.printf\n");//works
  
  log_info("Init gpio");
  pinMode(PIN::BTN_RED, INPUT);
  pinMode(PIN::BTN_YELLOW, INPUT);
  pinMode(PIN::MOVEMENT, INPUT);
  pinMode(PIN::BL_FAULT, INPUT);
  pinMode(PIN::HEATER, OUTPUT);
  pinMode(PIN::BRIGHTNESS, INPUT_ANALOG);

#if (defined(ARDUINO_LABATHOME_15_1) || defined(ARDUINO_LABATHOME_15_2))
  pinMode(PIN::RELAY, OUTPUT);
  pinMode(PIN::BL_SLEEP, OUTPUT);
  pinMode(PIN::BL_ISENSE, INPUT_ANALOG); // OPAMP2+
  pinMode(PIN::OPAMP3_M, INPUT_ANALOG);  // OPAMP3-
  pinMode(PIN::OPAMP3_P, INPUT_ANALOG);  // OPAMP3+
  pinMode(PIN::OPAMP3_Q, INPUT_ANALOG);  // OPAMP3+
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#ifdef ARDUINO_LABATHOME_15_2
  pinMode(PIN::ADC_2_24V, INPUT_ANALOG);
  pinMode(PIN::LCD_RESET, INPUT);
  pinMode(PIN::BL_RESET, OUTPUT);
  pinMode(PIN::PIN_PB12, INPUT);
  //pinMode(PIN::ADC_0, INPUT_ANALOG);
  //pinMode(PIN::ADC_1, INPUT_ANALOG);
#endif

#ifdef ARDUINO_LABATHOME_15_3
  pinMode(PIN::BL_SLEEP, OUTPUT);
  pinMode(PIN::BL_ISENSE, INPUT_ANALOG); // OPAMP2+
  pinMode(PIN::OPAMP3_M, INPUT_ANALOG);  // OPAMP3-
  pinMode(PIN::OPAMP3_P, INPUT_ANALOG);  // OPAMP3+
  pinMode(PIN::OPAMP3_Q, INPUT_ANALOG);  // OPAMP3+
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  HAL_ERROR_CHECK(HAL_OPAMP_Start(&hopamp2));
  pinMode(PIN::ADC_2_24V, INPUT_ANALOG);
  pinMode(PIN::LCD_RESET, INPUT);//because it is normally driven by the ESP32
  pinMode(PIN::BL_RESET, OUTPUT);
  pinMode(PIN::PIN_PB12, INPUT);
#endif

  log_info("Init Rotary Encoder");
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  TIM_SERVO->setPWM(SERVO3_CH, PC_3, 50, 0);

  TIM_FAN_LED_WHITE = new HardwareTimer(TIM15);
  TIM_FAN_LED_WHITE->setPWM(FAN_CH, PA_3_ALT1, 50, 0); // PA2 and PA3 changed from LabAtHome15.1 to 15.2
  TIM_FAN_LED_WHITE->setPWM(LED_WHITE_CH, PA_2_ALT1, 50, 0);

#elif defined(ARDUINO_LABATHOME_15_3)
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  TIM_SERVO->setPWM(SERVO3_CH, PC_3, 50, 0);

  TIM_FAN_LED_WHITE = new HardwareTimer(TIM15);
  TIM_FAN_LED_WHITE->setPWM(FAN_CH, PA_3_ALT1, 50, 0); // PA2 and PA3 changed from LabAtHome15.1 to 15.2
  TIM_FAN_LED_WHITE->setPWM(LED_WHITE_CH, PA_2_ALT1, 50, 0);

  log_info("Init ServoBus");
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  }
  log_info("Init StepperSerial");
  StepperSerial.begin(115200);
  pinMode(PIN::STEPPER_EN, OUTPUT);
  pinMode(PIN::FAN_SERVO4_STEPPER3_DIR, OUTPUT);
  pinMode(PIN::LED_WHITE_P_SERVO5_STEPPER3_STEP, OUTPUT);
  digitalWrite(PIN::STEPPER_EN, LOW); // Enable driver in hardware
  /*
    stepperdriver.begin();
    stepperdriver.toff(5);                 // Enables driver in software
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
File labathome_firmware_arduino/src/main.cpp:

#include <Arduino.h>
#include <Wire.h>
// I2C Konfiguration
constexpr uint8_t STM32_I2C_ADDRESS = 0x7E;
constexpr int I2C_SDA_PIN = 5;
constexpr int I2C_SCL_PIN = 6;
constexpr uint32_t I2C_FREQUENCY = 100000; // 100 kHz

// Pin Definitionen
constexpr gpio_num_t PIN_BTN_GREEN = (gpio_num_t)0;

constexpr gpio_num_t PIN_CANRX = (gpio_num_t)1;
constexpr gpio_num_t PIN_CANTX = (gpio_num_t)2;
constexpr gpio_num_t PIN_EXT_CS = (gpio_num_t)3;
constexpr gpio_num_t PIN_I2C_IRQ = (gpio_num_t)4;
constexpr gpio_num_t PIN_I2C_SDA = (gpio_num_t)5;
constexpr gpio_num_t PIN_I2C_SCL = (gpio_num_t)6;

constexpr gpio_num_t PIN_uSD_CMD = (gpio_num_t)7;
constexpr gpio_num_t PIN_LCD_CLK = (gpio_num_t)8;

constexpr gpio_num_t PIN_EXT_MISO = (gpio_num_t)9;
constexpr gpio_num_t PIN_EXT_CLK = (gpio_num_t)10;
constexpr gpio_num_t PIN_EXT_IO1 = (gpio_num_t)11;
constexpr gpio_num_t PIN_EXT_IO2 = (gpio_num_t)12;

constexpr gpio_num_t PIN_LED_WS2812 = (gpio_num_t)13;

constexpr gpio_num_t PIN_I2S_MCLK = (gpio_num_t)14;

constexpr gpio_num_t PIN_uSD_CLK = (gpio_num_t)15;
constexpr gpio_num_t PIN_uSD_D0 = (gpio_num_t)16;

constexpr gpio_num_t PIN_LCD_BL = (gpio_num_t)17;
constexpr gpio_num_t PIN_LCD_DC = (gpio_num_t)18;

constexpr gpio_num_t PIN_TXD0 = (gpio_num_t)43;
constexpr gpio_num_t PIN_RXD0 = (gpio_num_t)44;

constexpr gpio_num_t PIN_RS485_DI = (gpio_num_t)40;
constexpr gpio_num_t PIN_RS485_DE = (gpio_num_t)41;
constexpr gpio_num_t PIN_RS485_RO = (gpio_num_t)42;


constexpr gpio_num_t PIN_I2S_FS = (gpio_num_t)21;
constexpr gpio_num_t PIN_I2S_DAC = (gpio_num_t)45;
constexpr gpio_num_t PIN_EXT_MOSI = (gpio_num_t)46;
constexpr gpio_num_t PIN_I2S_ADC = (gpio_num_t)47;
constexpr gpio_num_t PIN_I2S_BCLK = (gpio_num_t)48;

constexpr gpio_num_t PIN_LCD_DAT = (gpio_num_t)38;
constexpr gpio_num_t PIN_LCD_RESET = (gpio_num_t)35;


constexpr gpio_num_t PIN_ONEWIRE = (gpio_num_t)39;
#include "communication.h"




void setup() {
    Serial.begin(115200);
    delay(1000);
    
    Serial.println("ESP32-S3 I2C Master Initialisierung");
    
    // I2C initialisieren
    Wire.begin(I2C_SDA_PIN, I2C_SCL_PIN);
    Wire.setClock(I2C_FREQUENCY);
    
    // Initialwerte für Send-Daten setzen
    initializeSendData();
    
    Serial.println("I2C Master bereit");
    Serial.printf("S2E_t Größe: %d Bytes\n", S2E_s);
    Serial.printf("E2S_t Größe: %d Bytes\n", E2S_s);
}

uint32_t lastDebugTime = 0;
void loop() {
    // Hauptkommunikationszyklus
    if (communicateWithSTM32()) {
        // Erfolgreiche Kommunikation
        processReceivedData();
        updateSendData();
        
        // Optional: Debug-Ausgabe
        if (millis() - lastDebugTime > 2000) {
            printDebugInfo();
            lastDebugTime = millis();
        }
    } else {
        // Fehlerbehandlung
        handleCommunicationError();
    }
    
    delay(10); // Kurze Pause zwischen den Zyklen
}



void processReceivedData() {
    // Hier die empfangenen Daten verarbeiten
    // Beispiel: Buttons, ADC-Werte, etc.
    
    if (receivedData.ButtonRed) {
        // Rote Button wurde gedrückt
        // Reaktion implementieren
    }
    
    if (receivedData.ButtonYellow) {
        // Gelbe Button wurde gedrückt
        // Reaktion implementieren
    }
    
    // ADC-Werte können hier verarbeitet werden
    // receivedData.Adc0, receivedData.Adc1, etc.
}

void updateSendData() {
    // Hier die zu sendenden Daten basierend auf
    // Programm-Logik aktualisieren
    
    // Beispiel: Fan-Geschwindigkeit basierend auf Temperatur steuern
    // if (receivedData.Adc2_24V > 2000) {
    //     sendData.Fan = 255; // Maximalgeschwindigkeit
    // } else {
    //     sendData.Fan = 128; // Halbe Geschwindigkeit
    // }
    
    // Beispiel: LED-Helligkeit vom Rotary Encoder übernehmen
    //sendData.LedPower = receivedData.Rotenc >> 8; // MSB des Encoders
}

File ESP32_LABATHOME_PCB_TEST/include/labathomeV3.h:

#include <inttypes.h>
#include <FastLED.h>
#include <Wire.h>
#include <OneWire.h>
#include <DallasTemperature.h>
#include <SparkFunBME280.h>
#include <BH1750.h>
#include <driver/mcpwm.h>
#include <driver/ledc.h>
#include <esp32-hal-ledc.h>

typedef uint8_t Pintype;

const Pintype PIN_R3_1 = 36;
const Pintype PIN_MOVEMENT = 39;
const Pintype PIN_POTI_T = 34;
const Pintype PIN_POTI = 35;
const Pintype PIN_SW_RED = 32;
const Pintype PIN_FAN_SENSE = 33;
const Pintype PIN_SERVO1 = 25;
const Pintype PIN_LED_STRIP = 26;
const Pintype PIN_SERVO2 = 27;
const Pintype PIN_ONEWIRE = 27;
const Pintype PIN_I2S_SCK = 14;
const Pintype PIN_FAN_DRIVE = 12;
const Pintype PIN_LED_POWER_WHITE = 13;
const Pintype PIN_LCD_MOSI = 23;
const Pintype PIN_I2C_SCL = 22;
const Pintype PIN_I2C_SDA = 21;
const Pintype PIN_LCD_RES = 19;
const Pintype PIN_LCD_CLK = 18;
const Pintype PIN_LCD_DC = 5;
const Pintype PIN_BUZZER = 17;
const Pintype PIN_R3_ON = 17;
const Pintype PIN_I2S_SD = 16;
const Pintype PIN_I2S_WS = 4;
const Pintype PIN_SW_GREEN = 0;
const Pintype PIN_HEATER = 2;
const Pintype PIN_SW_YELLOW = 15;


#define SERVO_MIN_PULSEWIDTH 500 //Minimum pulse width in microsecond
#define SERVO_MAX_PULSEWIDTH 2400 //Maximum pulse width in microsecond
#define SERVO_MAX_DEGREE 180 //Maximum angle in degree upto which servo can rotate

enum IO17_MODE
{
    RELAY,
    BUZZER,
};

enum class LED:uint8_t{
    LED_RED,
    LED_YELLOW,
    LED_GREEN,
    LED_3,
    LED_4,
    LED_5,
    LED_6,
    LED_7,
    

};

enum class Switch:uint8_t{
    SW_RED=PIN_SW_RED,
    SW_YELLOW=PIN_SW_YELLOW,
    SW_GREEN=PIN_SW_GREEN,
};

enum class Servo:uint8_t
{
    Servo1=0,
    Servo2=1,
};

class BSP
{    
    private:
        IO17_MODE io17;
    public:
        BSP(IO17_MODE io17):io17(io17)
        {

        }


        #define NUM_LEDS 8

        #define LED_TYPE WS2812B
        #define COLOR_ORDER GRB
        const uint8_t BRIGHTNESS = 50;
        const uint8_t FRAMES_PER_SECOND = 60;
        CRGBArray<NUM_LEDS> leds;
        // Setup a oneWire instance to communicate with any OneWire devices (not just Maxim/Dallas temperature ICs)
        OneWire oneWire();

        // Pass our oneWire reference to Dallas Temperature. 
        //DallasTemperature sensors(&oneWire);

        BME280 bme280;
        BH1750 bh1750;
        void initBoard()
        {
            
            pinMode(PIN_MOVEMENT, INPUT);
            pinMode(PIN_R3_1, INPUT);
            pinMode(PIN_POTI_T, ANALOG);
            pinMode(PIN_POTI, ANALOG);
            pinMode(PIN_SW_RED, INPUT_PULLUP);
            pinMode(PIN_FAN_SENSE, INPUT_PULLUP);
            FastLED.addLeds<LED_TYPE,PIN_LED_STRIP,COLOR_ORDER>(leds, NUM_LEDS).setCorrection(TypicalLEDStrip);
            FastLED.setBrightness( BRIGHTNESS );
            //oneWire.begin(27);
            pinMode(PIN_FAN_DRIVE, OUTPUT);
            pinMode(PIN_LED_POWER_WHITE, OUTPUT);
            Wire.begin(PIN_I2C_SDA, PIN_I2C_SCL, 100000);
            bme280.setI2CAddress(0x76); 
            if(bme280.beginI2C()){
                Serial.println("BME280 successfully initialized");
            }
            else
            {
                Serial.println("BME280 initialization failed");
            }
            if(bh1750.begin()){
                Serial.println("BH1750 successfully initialized");
            }
            else
            {
                Serial.println("BH1750 initialization failed");
            }
            
            
            if(io17==IO17_MODE::RELAY)
            {
                pinMode(PIN_R3_ON, OUTPUT);
            }
            
            pinMode(PIN_SW_GREEN, INPUT_PULLUP);
            pinMode(PIN_HEATER, OUTPUT);
            pinMode(PIN_SW_YELLOW, INPUT_PULLUP);

            //Servos
            mcpwm_gpio_init(MCPWM_UNIT_0, MCPWM0A, PIN_SERVO1);
            mcpwm_gpio_init(MCPWM_UNIT_0, MCPWM0B, PIN_SERVO2);
            mcpwm_config_t pwm_config;
            pwm_config.frequency = 50;    //frequency = 50Hz, i.e. for every servo motor time period should be 20ms
            pwm_config.cmpr_a = 0;    //duty cycle of PWMxA = 0
            pwm_config.cmpr_b = 0;    //duty cycle of PWMxb = 0
            pwm_config.counter_mode = MCPWM_UP_COUNTER;
            pwm_config.duty_mode = MCPWM_DUTY_MODE_0;
            mcpwm_init(MCPWM_UNIT_0, MCPWM_TIMER_0, &pwm_config);    //Configure PWM0A & PWM0B with above settings   

            //LED
            ledc_timer_config_t power_ledc_timer;
            power_ledc_timer.duty_resolution = LEDC_TIMER_13_BIT; // resolution of PWM duty
            power_ledc_timer.freq_hz = 5000;                      // frequency of PWM signal
            power_ledc_timer.speed_mode = LEDC_HIGH_SPEED_MODE;           // timer mode
            power_ledc_timer.timer_num = LEDC_TIMER_0;            // timer index
            ledc_timer_config(&power_ledc_timer);

            ledc_channel_config_t ledc_channel;
            ledc_channel.channel    = LEDC_CHANNEL_0;
            ledc_channel.duty       = 0;
            ledc_channel.gpio_num   = PIN_LED_POWER_WHITE;
            ledc_channel.speed_mode = LEDC_HIGH_SPEED_MODE;
            ledc_channel.hpoint     = 0;
            ledc_channel.timer_sel  = LEDC_TIMER_0;

            ledc_channel_config(&ledc_channel);

            if(io17==IO17_MODE::BUZZER)
            {
                ledcSetup(2, 2000, 8);
                ledcAttachPin(PIN_BUZZER, 2);
            }
        
        }

        void startBuzzer(double freq)
        {
            if(io17!=IO17_MODE::BUZZER) return;
            ledcWriteTone(2, freq);
        }

        void endBuzzer()
        {
            ledcWrite(2, 0);
        }
        
        void setLEDState(LED led, CRGB state)
        {
            leds[(uint8_t)led]=state;
            FastLED.show();
        }

        void setRELAYState(bool state)
        {
            if(io17!=IO17_MODE::RELAY) return;
            digitalWrite(PIN_R3_ON, state);
        }

        void setLED_POWER_WHITE_DUTY(uint8_t percent)
        {
            if(percent>100) percent=100;
            uint32_t duty =((1<<13)*percent)/100;
            ledc_set_duty(LEDC_HIGH_SPEED_MODE, LEDC_CHANNEL_0, duty);
            ledc_update_duty(LEDC_HIGH_SPEED_MODE, LEDC_CHANNEL_0);
        }
        bool getButtonIsPressed(Switch theSwitch)
        {
            return !digitalRead((uint8_t)theSwitch);
        }

        bool isMovementDetected()
        {
            return digitalRead(PIN_MOVEMENT);
        }

        void setServo (Servo servo, uint32_t angle_0_to_180)
        {
            uint32_t cal_pulsewidth = (SERVO_MIN_PULSEWIDTH + (((SERVO_MAX_PULSEWIDTH - SERVO_MIN_PULSEWIDTH) * (angle_0_to_180)) / (SERVO_MAX_DEGREE)));
            switch(servo)
            {
                case Servo::Servo1:
                    mcpwm_set_duty_in_us(MCPWM_UNIT_0, MCPWM_TIMER_0, MCPWM_OPR_A, cal_pulsewidth);
                    break;
                case Servo::Servo2:
                    mcpwm_set_duty_in_us(MCPWM_UNIT_0, MCPWM_TIMER_0, MCPWM_OPR_B, cal_pulsewidth);
                    break;
                default:
                    break;
            }
        }
};

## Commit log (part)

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2020-04-18 Improved Layout
2020-05-07 PCB REV2
2020-05-07 testwebserver initial
2020-06-18 PCB V2 RC1
2020-06-18 First fuction block implementation
2020-06-18 VSCode Workspace
2020-06-19 Better 3D models
2020-06-22 PCB V2 as ordered
2020-06-28 Slight optimizations in PCB
2020-07-25 Case design
2020-07-25 Firmware Various Updates
2020-08-11 PCB V4 as ordered at JLCPCB
2020-08-11 Arduino based test software for produced boards
2020-08-25 PCB last version without SMD
2020-08-29 PCB labathomev5 as ordered at jlcpcb
2020-09-20 Various big changes (sorry for beeing rude here...)
2020-09-26 labathome - first break through - simple and/or/rs working :-)
2020-10-02 PID-Controller
2020-10-14 Overall unspecific update
2020-10-16 V0.1 ready for testing :-)
2020-11-02 Simulation Mode in WebUI
2020-11-14 heaterEmergencyShutdown fix
2020-12-13 Bump ini from 1.3.5 to 1.3.8 in /rtttl2binary
    Bumps [ini](https://github.com/isaacs/ini) from 1.3.5 to 1.3.8.
    - [Release notes](https://github.com/isaacs/ini/releases)
    - [Commits](https://github.com/isaacs/ini/compare/v1.3.5...v1.3.8)
2021-03-10 Bump elliptic from 6.5.3 to 6.5.4 in /webui
    Bumps [elliptic](https://github.com/indutny/elliptic) from 6.5.3 to 6.5.4.
    - [Release notes](https://github.com/indutny/elliptic/releases)
    - [Commits](https://github.com/indutny/elliptic/compare/v6.5.3...v6.5.4)
2021-03-31 Bump y18n from 3.2.1 to 3.2.2 in /rtttl2binary
    Bumps [y18n](https://github.com/yargs/y18n) from 3.2.1 to 3.2.2.
    - [Release notes](https://github.com/yargs/y18n/releases)
    - [Changelog](https://github.com/yargs/y18n/blob/master/CHANGELOG.md)
    - [Commits](https://github.com/yargs/y18n/commits)
2021-05-11 Bump hosted-git-info from 2.8.8 to 2.8.9 in /webui
    Bumps [hosted-git-info](https://github.com/npm/hosted-git-info) from 2.8.8 to 2.8.9.
    - [Release notes](https://github.com/npm/hosted-git-info/releases)
    - [Changelog](https://github.com/npm/hosted-git-info/blob/v2.8.9/CHANGELOG.md)
    - [Commits](https://github.com/npm/hosted-git-info/compare/v2.8.8...v2.8.9)
2021-05-11 Bump hosted-git-info from 2.8.8 to 2.8.9 in /rtttl2binary
    Bumps [hosted-git-info](https://github.com/npm/hosted-git-info) from 2.8.8 to 2.8.9.
    - [Release notes](https://github.com/npm/hosted-git-info/releases)
    - [Changelog](https://github.com/npm/hosted-git-info/blob/v2.8.9/CHANGELOG.md)
    - [Commits](https://github.com/npm/hosted-git-info/compare/v2.8.8...v2.8.9)
2021-06-01 lab@home5.3 as ordered at jlcpcb
2021-06-04 I2S-Amp --> Analog (damn cheap) Amp
2021-08-09 labathome V6 as ordered at JLCPCB
2021-08-12 Bump path-parse from 1.0.6 to 1.0.7 in /rtttl2binary
    Bumps [path-parse](https://github.com/jbgutierrez/path-parse) from 1.0.6 to 1.0.7.
    - [Release notes](https://github.com/jbgutierrez/path-parse/releases)
    - [Commits](https://github.com/jbgutierrez/path-parse/commits/v1.0.7)
    ---
    updated-dependencies:
    - dependency-name: path-parse
2021-09-14 Switched to CMAKE
2021-09-14 Added option description for PCB
2021-11-25 pcb V10 as ordered at JLCPCB
2022-01-01 labathome v11 as ordered @ JLCPCB
2022-01-07 Moved all components to esp-idf components repository
2022-02-11 Bump node-sass from 4.14.1 to 7.0.0 in /labathome_webui
    Bumps [node-sass](https://github.com/sass/node-sass) from 4.14.1 to 7.0.0.
    - [Release notes](https://github.com/sass/node-sass/releases)
    - [Changelog](https://github.com/sass/node-sass/blob/master/CHANGELOG.md)
    - [Commits](https://github.com/sass/node-sass/compare/v4.14.1...v7.0.0)
    ---
    updated-dependencies:
2022-03-02 All SMD components orderable @ JLCPCB
2022-03-27 Updated capacitor JLCPCB, Removed unnecessary Files
2022-03-30 Bump minimist from 1.2.5 to 1.2.6 in /labathome_webui
    Bumps [minimist](https://github.com/substack/minimist) from 1.2.5 to 1.2.6.
    - [Release notes](https://github.com/substack/minimist/releases)
    - [Commits](https://github.com/substack/minimist/compare/1.2.5...1.2.6)
    ---
    updated-dependencies:
    - dependency-name: minimist
2022-04-04 Migration to IDF5.0
2022-04-08 Sicherung
2022-05-06 Various
2022-05-12 Bump copy-props from 2.0.4 to 2.0.5 in /rtttl2binary
    Bumps [copy-props](https://github.com/gulpjs/copy-props) from 2.0.4 to 2.0.5.
    - [Release notes](https://github.com/gulpjs/copy-props/releases)
    - [Changelog](https://github.com/gulpjs/copy-props/blob/master/CHANGELOG.md)
    - [Commits](https://github.com/gulpjs/copy-props/compare/2.0.4...2.0.5)
    ---
    updated-dependencies:
2022-05-12 Bump copy-props from 2.0.4 to 2.0.5 in /labathome_webui
    Bumps [copy-props](https://github.com/gulpjs/copy-props) from 2.0.4 to 2.0.5.
    - [Release notes](https://github.com/gulpjs/copy-props/releases)
    - [Changelog](https://github.com/gulpjs/copy-props/blob/master/CHANGELOG.md)
    - [Commits](https://github.com/gulpjs/copy-props/compare/2.0.4...2.0.5)
    ---
    updated-dependencies:
2022-05-12 Bump lodash from 4.17.20 to 4.17.21 in /labathome_webui
    Bumps [lodash](https://github.com/lodash/lodash) from 4.17.20 to 4.17.21.
    - [Release notes](https://github.com/lodash/lodash/releases)
    - [Commits](https://github.com/lodash/lodash/compare/4.17.20...4.17.21)
    ---
    updated-dependencies:
    - dependency-name: lodash
2022-05-12 Refactoring; configmanager, otamanager
2022-05-12 Deleted old pcb version - never go back to these times ;-)
2022-05-23 Reorganisation
2022-06-09 component for AHT21 sensor
2022-06-22 Bugfix: digital amplifier not in standby
2022-07-01 Boris Integration; some code rework
2022-07-19 Getting ptnchen running; borisuserdlls
2022-07-20 Addes ptnchen pcb
2022-09-03 Minor fixes
2022-09-08 Updated PCB: nRF24l01, SIM7080, LoRa module
2022-11-10 Bump minimatch from 3.0.4 to 3.1.2 in /rtttl2binary
    Bumps [minimatch](https://github.com/isaacs/minimatch) from 3.0.4 to 3.1.2.
    - [Release notes](https://github.com/isaacs/minimatch/releases)
    - [Commits](https://github.com/isaacs/minimatch/compare/v3.0.4...v3.1.2)
    ---
    updated-dependencies:
    - dependency-name: minimatch
2022-12-07 Bump decode-uri-component from 0.2.0 to 0.2.2 in /rtttl2binary
    Bumps [decode-uri-component](https://github.com/SamVerschueren/decode-uri-component) from 0.2.0 to 0.2.2.
    - [Release notes](https://github.com/SamVerschueren/decode-uri-component/releases)
    - [Commits](https://github.com/SamVerschueren/decode-uri-component/compare/v0.2.0...v0.2.2)
    ---
    updated-dependencies:
    - dependency-name: decode-uri-component
2022-12-07 Bump qs and express in /testwebserver
    Bumps [qs](https://github.com/ljharb/qs) to 6.11.0 and updates ancestor dependency [express](https://github.com/expressjs/express). These dependencies need to be updated together.
    Updates `qs` from 6.7.0 to 6.11.0
    - [Release notes](https://github.com/ljharb/qs/releases)
    - [Changelog](https://github.com/ljharb/qs/blob/main/CHANGELOG.md)
    - [Commits](https://github.com/ljharb/qs/compare/v6.7.0...v6.11.0)
    Updates `express` from 4.17.1 to 4.18.2
2022-12-08 LTSpice Simulation & minor optical fixes
2023-01-24 Bump cookiejar from 2.1.3 to 2.1.4 in /labathome_webui
    Bumps [cookiejar](https://github.com/bmeck/node-cookiejar) from 2.1.3 to 2.1.4.
    - [Release notes](https://github.com/bmeck/node-cookiejar/releases)
    - [Commits](https://github.com/bmeck/node-cookiejar/commits)
    ---
    updated-dependencies:
    - dependency-name: cookiejar
2023-08-08 Modbus Firmware
2023-08-09 Switch UART
    Programming port (GPIO1 and 3) are the modbus port now. console output shoud be routed to GPIO 21 (menuconfig
2023-09-03 Udated flash website
2023-09-24 Reading DS18B20
2023-10-09 New sensor values
2023-10-20 Fix Movement Sensor
2024-06-27 PCB_v15 wip
2024-06-28 pcb15 WIP
2024-07-01 labathome15 v0.0.1
2024-07-05 initial version of labathome_firmware_stm32
2024-07-05 labathome_pcb15 ready for first review
2024-07-05 labathome_pcb15
2024-07-06 labathome_pcb5 ready for review, 2nd
2024-07-08 Various PCB and Code updates after review from Jana Marie Hemsing. Big Thankyou
2024-07-08 Ooops, did not test to build it...
2024-07-08 Final PCB as ordered @ JLCPCB
2024-07-16 Various updates
2024-08-16 Added stm32 arduino firmware
2024-08-20 Updates in PCB, arduino test firmware
2024-08-20 Cosmetics
2024-08-20 Re-enumerate Servos and Fans
2024-08-20 Update Modbus firmware (untested)
2024-08-22 Cosmetics (improved ground planes, more vias)
2024-08-22 Various bugfixes for the stm32 arduino firmware
2024-08-23 Various Bugfixes after testing modbus and open loop heater experiment
2024-08-29 Show state on display; minor cosmetics
2024-08-29 nau88c22 45deg
2024-09-01 Fix Easteregg
2024-09-01 OutputOneLineStatus -->DoMonitoring
2024-09-02 PCB update IP5306 I2C
2024-09-03 4 Layers
2024-09-04 labathome 15.1 as ordered @ JLCPCB
2024-09-05 Update LabathomeMapping.md
    Add general informations and functioncodes
2024-09-10 brushless motor firmware
2024-09-15 lsm6ds3 + kalman
2024-09-17 Labathome Heater control loop working point
2024-09-20 Bump vite from 5.3.3 to 5.4.6 in /espidf-component-labathome/web
    Bumps [vite](https://github.com/vitejs/vite/tree/HEAD/packages/vite) from 5.3.3 to 5.4.6.
    - [Release notes](https://github.com/vitejs/vite/releases)
    - [Changelog](https://github.com/vitejs/vite/blob/v5.4.6/packages/vite/CHANGELOG.md)
    - [Commits](https://github.com/vitejs/vite/commits/v5.4.6/packages/vite)
    ---
    updated-dependencies:
2024-09-24 Bump rollup from 4.18.1 to 4.22.4 in /espidf-component-labathome/web
    Bumps [rollup](https://github.com/rollup/rollup) from 4.18.1 to 4.22.4.
    - [Release notes](https://github.com/rollup/rollup/releases)
    - [Changelog](https://github.com/rollup/rollup/blob/master/CHANGELOG.md)
    - [Commits](https://github.com/rollup/rollup/compare/v4.18.1...v4.22.4)
    ---
    updated-dependencies:
2024-10-01 Code to test the accessability of a serial port
2024-10-03 ec11 smd, LCD Reset from ESP32 with jumper, six servos
2024-10-11 Updated PCB, sensprs as JSON
2024-10-13 IP5306
2024-10-14 Pushed microSD up
2024-10-17 TPS2116
2024-10-17 Labathome 15.2 as ordered at JLCPCB
2024-10-31 Database based build process
2024-11-04 PCB 15.2 as ordered @ JLCPCB; database backed build process
2024-11-05 New Function Block ConstantINTEGER
2024-11-06 Fixes for 15.2 and 15.ß
2024-11-11 Fixes / Refactoring
2024-11-15 Added Stepper Motors (initial)
2024-11-16 Fixes
2024-11-22 PCB update; DRC check passed; optimized routing
2024-11-22 Layout improvement; use common enable signal for steppers
2024-11-26 Optimized PCB
2024-11-26 Prepared new 15_3 board version with stepper motor drivers
2024-11-26 Added flatbuffers
2024-11-26 Added SVG collection from fontawesome
2024-11-26 Bump vite from 5.3.3 to 5.4.11 in /espidf-component-labathome/web
    Bumps [vite](https://github.com/vitejs/vite/tree/HEAD/packages/vite) from 5.3.3 to 5.4.11.
    - [Release notes](https://github.com/vitejs/vite/releases)
    - [Changelog](https://github.com/vitejs/vite/blob/main/packages/vite/CHANGELOG.md)
    - [Commits](https://github.com/vitejs/vite/commits/v5.4.11/packages/vite)
    ---
    updated-dependencies:
2024-11-27 Change communication from XHTTP to Websocket
2024-11-27 heater_controller got transformed to websocket and flatbuffers
2024-11-30 Continued with severe refactoring. Now builds, but completely untested
2024-12-02 Google Api Key
2024-12-19 Bus servos
2024-12-19 Build Automation improved
2025-01-17 Merged
2025-01-17 Merge
2025-01-20 Improved building process
2025-01-23 Bugfixes, moved testserver websocket handlers to external package
2025-01-23 Minor improments on pcb
2025-01-26 Added usersettings plugin
2025-01-28 Minor changes
2025-03-06 Labathome PCB -> KICAD 9
2025-03-09 Bugxes/Improvements
2025-03-11 Fixed heaterexperiment crash; renamed all flatbuffers to include namespace
2025-03-21 Update labathome.code-workspace
2025-03-21 ignore boards_info.json
2025-03-25 Fix Hostname/AP name
2025-03-25 Runs without oneWireBus and stm32
2025-10-31 Updated debug output
2025-10-31 Added pin definitions
